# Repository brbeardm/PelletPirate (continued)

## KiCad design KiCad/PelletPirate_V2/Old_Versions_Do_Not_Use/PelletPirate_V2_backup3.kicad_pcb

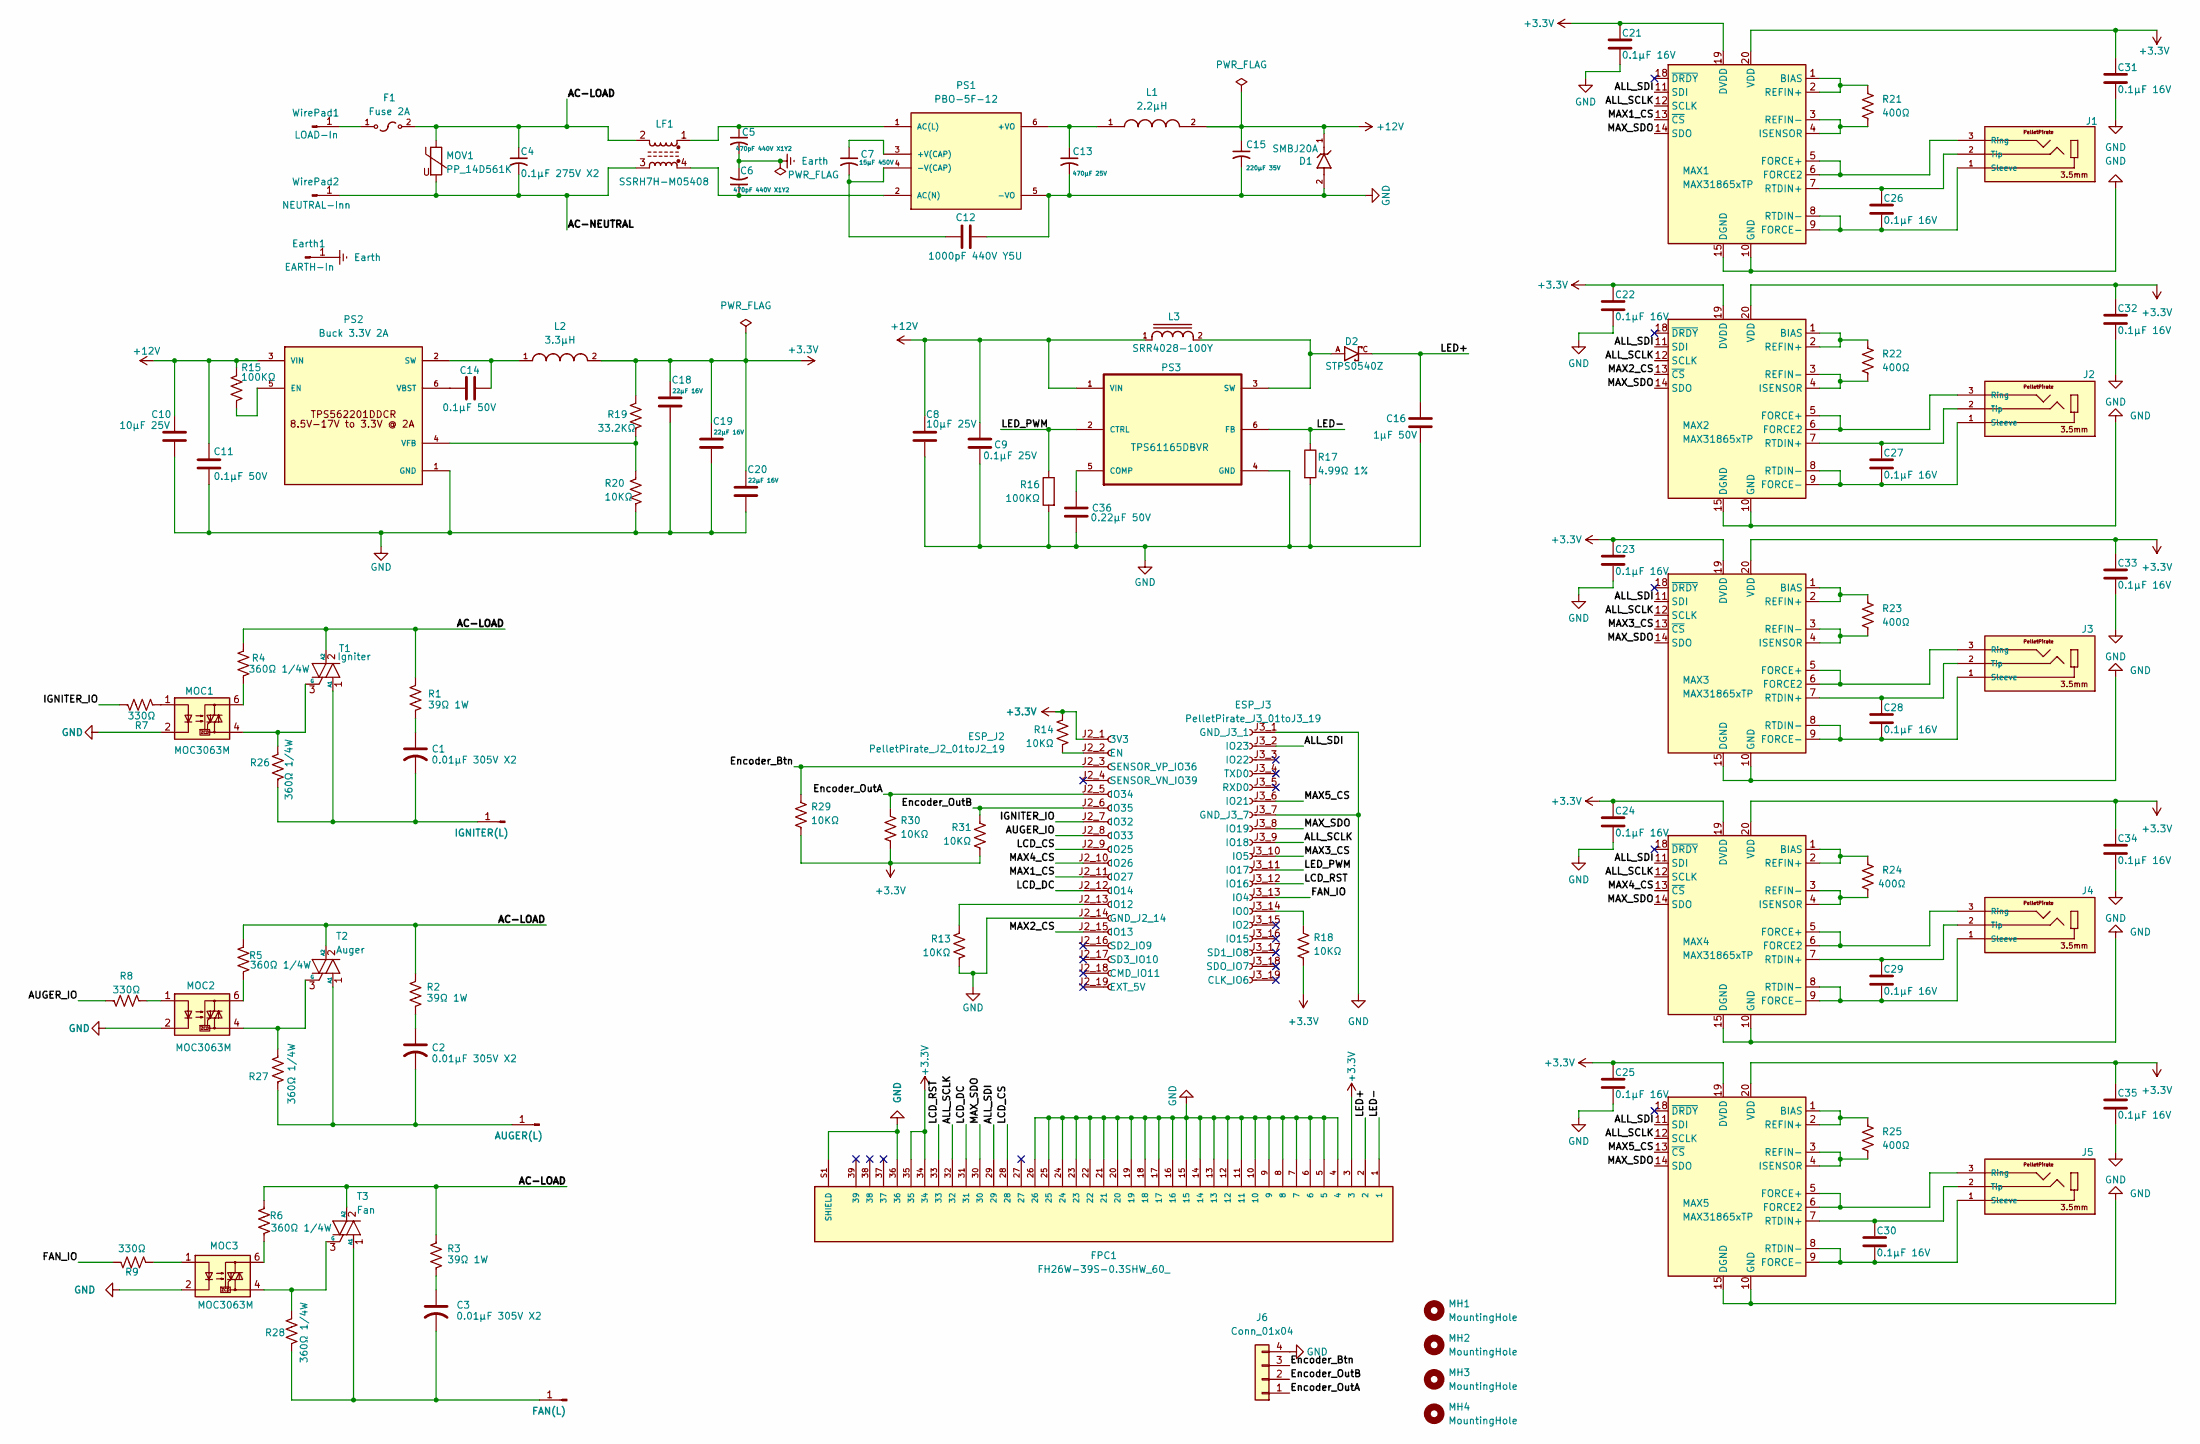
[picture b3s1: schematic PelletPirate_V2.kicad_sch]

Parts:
C1, C2, C3: 0.01µF 305V X2; C_Rect_L13.0mm_W4.0mm_P10.00mm_FKS3_FKP3_MKS4
C4: 0.1µF 275V X2; C_Rect_L13.0mm_W6.0mm_P10.00mm_FKS3_FKP3_MKS4
C5, C6: 470pF 440V X1Y2; C_Disc_D7.5mm_W5.0mm_P7.50mm
C7: 15µF 450V; CP_Radial_D10.0mm_P5.00mm
C8, C10: 10µF 25V; C_1206_3216Metric
C9: 0.1µF 25V; C_0805_2012Metric
C11, C14: 0.1µF 50V; C_0805_2012Metric
C12: 1000pF 440V Y5U; C_Disc_D7.5mm_W5.0mm_P7.50mm
C13: 470µF 25V; CP_Radial_D10.0mm_P5.00mm
C15: 220µF 35V; CP_Radial_D8.0mm_P3.50mm
C16: 1µF 50V; C_0805_2012Metric_Pad1.18x1.45mm_HandSolder
C18, C19, C20: 22µF 16V; C_1206_3216Metric
C21, C22, C23, C24, C25, C26, C27, C28, C29, C30, C31, C32, C33, C34, C35: 0.1µF 16V; C_0805_2012Metric
C36: 0.22µF 50V; C_0805_2012Metric_Pad1.18x1.45mm_HandSolder
D1: SMBJ20A; DIOM5436X261N_PelletPirate; PARTREV JC.07/04/25 v4; DigiKey_Part_Number SMBJ20ALFCT-ND
D2: STPS0540Z; SOD-123
ESP_J2: PelletPirate_J2_01toJ2_19; PinHeader_J2x19_P2.54mm_Vertical_PelletPirate
ESP_J3: PelletPirate_J3_01toJ3_19; PinHeader_J3x19_P2.54mm_Vertical_PelletPirate
Earth1: EARTH-In; SolderWire-2.5sqmm_1x01_D2.4mm_OD4.4mm
F1: Fuse 2A; SCHURTER_0031.8201; DigiKey_Part_Number 486-1258-ND
FPC1: FH26W-39S-0.3SHW_60_; HRS_FH26W-39S-0.3SHW_60_; PARTREV N/A
J1, J2, J3, J4, J5: SJ1-3523NG_Jack_PP; CUI_SJ1-3523NG_PelletPirate; PARTREV 1.01
J6: Conn_01x04; Hirose_DF13-04P-1.25DSA_1x04_P1.25mm_Vertical
L1: 2.2µH; IND_LQH3NPH2R2MMEL
L2: 3.3µH; IND_LQH43PN3R3M26L; PARTREV N/A
L3: SRR4028-100Y; SRR4028
LF1: SSRH7H-M05408; Kemet_Choke_SSRH7H_M05408
MAX1, MAX2, MAX3, MAX4, MAX5: MAX31865xTP; TQFN-20-1EP_5x5mm_P0.65mm_EP3.25x3.25mm
MH1, MH2, MH3, MH4: MountingHole; MountingHole_3.2mm_M3
MOC1, MOC2, MOC3: MOC3063M; MOC3063M-PP2
MOV1: PP_14D561K; Varistor_14mm_p7.5mm
PS1: PBO-5F-12; PBO-5F-12_pp2; PARTREV 1.0
PS2: Buck 3.3V 2A; SOT95P280X110-6N; PARTREV A
PS3: TPS61165DBVR; SOT95P280X145-6N
R1, R2, R3: 39Ω 1W; R_2512_6332Metric
R4, R5, R6, R26, R27, R28: 360Ω 1/4W; R_1206_3216Metric
R7, R8, R9: 330Ω; R_0805_2012Metric_Pad1.20x1.40mm_HandSolder
R13, R14, R18, R20, R29, R30, R31: 10KΩ; R_0805_2012Metric_Pad1.20x1.40mm_HandSolder
R15: 100KΩ; R_0805_2012Metric_Pad1.20x1.40mm_HandSolder
R16: 100KΩ; R_0603_1608Metric_Pad0.98x0.95mm_HandSolder
R17: 4.99Ω 1%; R_1206_3216Metric_Pad1.30x1.75mm_HandSolder
R19: 33.2KΩ; R_0805_2012Metric_Pad1.20x1.40mm_HandSolder
R21, R22, R23, R24, R25: 400Ω; R_1206_3216Metric
T1: Igniter; TO-220-3_Vertical
T2: Auger; TO-220-3_Vertical
T3: Fan; TO-220-3_Vertical
WirePad1: LOAD-In; SolderWire-2.5sqmm_1x01_D2.4mm_OD4.4mm
WirePad2: NEUTRAL-Inn; SolderWire-2.5sqmm_1x01_D2.4mm_OD4.4mm
WirePad3: IGNITER(L); SolderWire-2.5sqmm_1x01_D2.4mm_OD3.6mm
WirePad4: AUGER(L); SolderWire-2.5sqmm_1x01_D2.4mm_OD3.6mm
WirePad5: FAN(L); SolderWire-2.5sqmm_1x01_D2.4mm_OD3.6mm

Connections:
+3.3V: C18.1, C19.1, C20.1, C21.2, C22.2, C23.2, C24.2, C25.2, C31.2, C32.2, C33.2, C34.2, C35.2, ESP_J2.J2_1 (3V3), FPC1.3, FPC1.34, FPC1.35, L2.2, MAX1.19 (DVDD), MAX1.20 (VDD), MAX2.19 (DVDD), MAX2.20 (VDD), MAX3.19 (DVDD), MAX3.20 (VDD), MAX4.19 (DVDD), MAX4.20 (VDD), MAX5.19 (DVDD), MAX5.20 (VDD), R14.1, R18.2, R19.1, R29.2, R30.2, R31.2; also elsewhere on the board
+12V: C8.1, C9.1, C10.1, C11.2, C15.1, D1.1, L1.2, L3.1, PS2.3 (VIN), PS3.1 (VIN), R15.1
/AC-LOAD: C4.1, F1.2, LF1.2, MOV1.1, R1.1, R2.1, R3.1, R4.2, R5.2, R6.1, T1.2 (A2), T2.2 (A2), T3.2 (A2)
/AC-NEUTRAL: C4.2, LF1.3, MOV1.2, WirePad2.1 (Pin_1_1); also elsewhere on the board
/ALL_SCLK: ESP_J3.J3_9 (IO18), FPC1.32, MAX1.12 (SCLK), MAX2.12 (SCLK), MAX3.12 (SCLK), MAX4.12 (SCLK), MAX5.12 (SCLK); also elsewhere on the board
/ALL_SDI: ESP_J3.J3_2 (IO23), FPC1.29, MAX1.11 (SDI), MAX2.11 (SDI), MAX3.11 (SDI), MAX4.11 (SDI), MAX5.11 (SDI); also elsewhere on the board
/AUGER_IO: ESP_J2.J2_8 (IO33), R8.2; also elsewhere on the board
/Encoder_Btn: ESP_J2.J2_3 (SENSOR_VP_IO36), J6.3, R29.1; also elsewhere on the board
/Encoder_OutA: ESP_J2.J2_5 (IO34), J6.1, R30.1; also elsewhere on the board
/Encoder_OutB: ESP_J2.J2_6 (IO35), J6.2, R31.1; also elsewhere on the board
/FAN_IO: ESP_J3.J3_13 (IO4), R9.1; also elsewhere on the board
/IGNITER_IO: ESP_J2.J2_7 (IO32), R7.2; also elsewhere on the board
/LCD_CS: ESP_J2.J2_9 (IO25), FPC1.28; also elsewhere on the board
/LCD_DC: ESP_J2.J2_12 (IO14), FPC1.31; also elsewhere on the board
/LCD_RST: ESP_J3.J3_12 (IO16), FPC1.33; also elsewhere on the board
/LED+: C16.1, D2.C, FPC1.2
/LED-: FPC1.1, PS3.6 (FB), R17.1
/LED_PWM: ESP_J3.J3_11 (IO17), PS3.2 (CTRL), R16.1; also elsewhere on the board
/MAX1_CS: ESP_J2.J2_11 (IO27), MAX1.13 (~CS); also elsewhere on the board
/MAX2_CS: ESP_J2.J2_15 (IO13), MAX2.13 (~CS); also elsewhere on the board
/MAX3_CS: ESP_J3.J3_10 (IO5), MAX3.13 (~CS); also elsewhere on the board
/MAX4_CS: ESP_J2.J2_10 (IO26), MAX4.13 (~CS); also elsewhere on the board
/MAX5_CS: ESP_J3.J3_6 (IO21), MAX5.13 (~CS); also elsewhere on the board
/MAX_SDO: ESP_J3.J3_8 (IO19), FPC1.30, MAX1.14 (SDO), MAX2.14 (SDO), MAX3.14 (SDO), MAX4.14 (SDO), MAX5.14 (SDO); also elsewhere on the board
Earth: C5.2, C6.2, Earth1.1 (Pin_1_1)
GND: C8.2, C9.2, C10.2, C11.1, C12.2, C13.2, C15.2, C16.2, C18.2, C19.2, C20.2, C21.1, C22.1, C23.1, C24.1, C25.1, C31.1, C32.1, C33.1, C34.1, C35.1, C36.2, D1.2, ESP_J2.J2_14 (GND_J2_14), ESP_J3.J3_1 (GND_J3_1), ESP_J3.J3_7 (GND_J3_7), FPC1.4, FPC1.5, FPC1.6, FPC1.7, FPC1.8, FPC1.9, FPC1.10, FPC1.11, FPC1.12, FPC1.13, FPC1.14, FPC1.15, FPC1.16, FPC1.17, FPC1.18, FPC1.19, FPC1.20, FPC1.21, FPC1.22, FPC1.23, FPC1.24, FPC1.25, FPC1.26, FPC1.36, FPC1.S1 (SHIELD), FPC1.S2 (SHIELD), J6.4, MAX1.10 (GND), MAX1.15 (DGND), MAX1.16 (GND), MAX1.21 (GND), MAX2.10 (GND), MAX2.15 (DGND), MAX2.16 (GND), MAX2.21 (GND), MAX3.10 (GND), MAX3.15 (DGND), MAX3.16 (GND), MAX3.21 (GND), MAX4.10 (GND), MAX4.15 (DGND), MAX4.16 (GND), MAX4.21 (GND), MAX5.10 (GND), MAX5.15 (DGND), MAX5.16 (GND), MAX5.21 (GND), MOC1.2, MOC2.2, MOC3.2, PS1.5 (-VO), PS2.1 (GND), PS3.4 (GND), R13.2, R16.2, R17.2, R20.2; also elsewhere on the board
unnamed: C1.1, R1.2
unnamed: C2.1, R2.2
unnamed: C3.1, R3.2
unnamed 29: ESP_J2.J2_2 (EN), R14.2; also elsewhere on the board
unnamed 30: ESP_J3.J3_14 (IO0), R18.1; also elsewhere on the board
unnamed 31: ESP_J2.J2_13 (IO12), R13.1; also elsewhere on the board
unnamed: J1.3 (Ring), MAX1.5 (FORCE+), MAX1.6 (FORCE2)
unnamed: C26.1, J1.1 (Sleeve), MAX1.8 (RTDIN-), MAX1.9 (FORCE-)
unnamed: C26.2, J1.2 (Tip), MAX1.7 (RTDIN+)
unnamed: J2.3 (Ring), MAX2.5 (FORCE+), MAX2.6 (FORCE2)
unnamed: C27.1, J2.1 (Sleeve), MAX2.8 (RTDIN-), MAX2.9 (FORCE-)
unnamed: C27.2, J2.2 (Tip), MAX2.7 (RTDIN+)
unnamed: J3.3 (Ring), MAX3.5 (FORCE+), MAX3.6 (FORCE2)
unnamed: C28.1, J3.1 (Sleeve), MAX3.8 (RTDIN-), MAX3.9 (FORCE-)
unnamed: C28.2, J3.2 (Tip), MAX3.7 (RTDIN+)
unnamed: J4.3 (Ring), MAX4.5 (FORCE+), MAX4.6 (FORCE2)
unnamed: C29.1, J4.1 (Sleeve), MAX4.8 (RTDIN-), MAX4.9 (FORCE-)
unnamed: C29.2, J4.2 (Tip), MAX4.7 (RTDIN+)
unnamed: J5.3 (Ring), MAX5.5 (FORCE+), MAX5.6 (FORCE2)
unnamed: C30.1, J5.1 (Sleeve), MAX5.8 (RTDIN-), MAX5.9 (FORCE-)
unnamed: C30.2, J5.2 (Tip), MAX5.7 (RTDIN+)
unnamed: MAX1.1 (BIAS), MAX1.2 (REFIN+), R21.1
unnamed: MAX1.3 (REFIN-), MAX1.4 (ISENSOR), R21.2
unnamed: MAX2.1 (BIAS), MAX2.2 (REFIN+), R22.1
unnamed: MAX2.3 (REFIN-), MAX2.4 (ISENSOR), R22.2
unnamed: MAX3.1 (BIAS), MAX3.2 (REFIN+), R23.1
unnamed: MAX3.3 (REFIN-), MAX3.4 (ISENSOR), R23.2
unnamed: MAX4.1 (BIAS), MAX4.2 (REFIN+), R24.1
unnamed: MAX4.3 (REFIN-), MAX4.4 (ISENSOR), R24.2
unnamed: MAX5.1 (BIAS), MAX5.2 (REFIN+), R25.1
unnamed: MAX5.3 (REFIN-), MAX5.4 (ISENSOR), R25.2
unnamed: MOC1.1, R7.1
unnamed: MOC1.6, R4.1
unnamed: MOC2.1, R8.1
unnamed: MOC2.6, R5.1
unnamed: MOC3.1, R9.2
unnamed: MOC3.6, R6.2
unnamed: C7.1, PS1.3 (+V(CAP))
unnamed: C13.1, L1.1, PS1.6 (+VO)
unnamed: C7.2, C12.1, PS1.4 (-V(CAP))
unnamed: C5.1, LF1.1, PS1.1 (AC(L))
unnamed: C6.1, LF1.4, PS1.2 (AC(N))
unnamed: PS2.5 (EN), R15.2
unnamed: C14.2, L2.1, PS2.2 (SW)
unnamed: C14.1, PS2.6 (VBST)
unnamed: PS2.4 (VFB), R19.2, R20.1
unnamed: C36.1, PS3.5 (COMP)
unnamed: D2.A, L3.2, PS3.3 (SW)
unnamed: C1.2, R26.2, T1.1 (A1), WirePad3.1 (Pin_1_1)
unnamed: MOC1.4, R26.1, T1.3 (G)
unnamed: C2.2, R27.2, T2.1 (A1), WirePad4.1 (Pin_1_1)
unnamed: MOC2.4, R27.1, T2.3 (G)
unnamed: C3.2, R28.2, T3.1 (A1), WirePad5.1 (Pin_1_1)
unnamed: MOC3.4, R28.1, T3.3 (G)
unnamed: F1.1, WirePad1.1 (Pin_1_1)

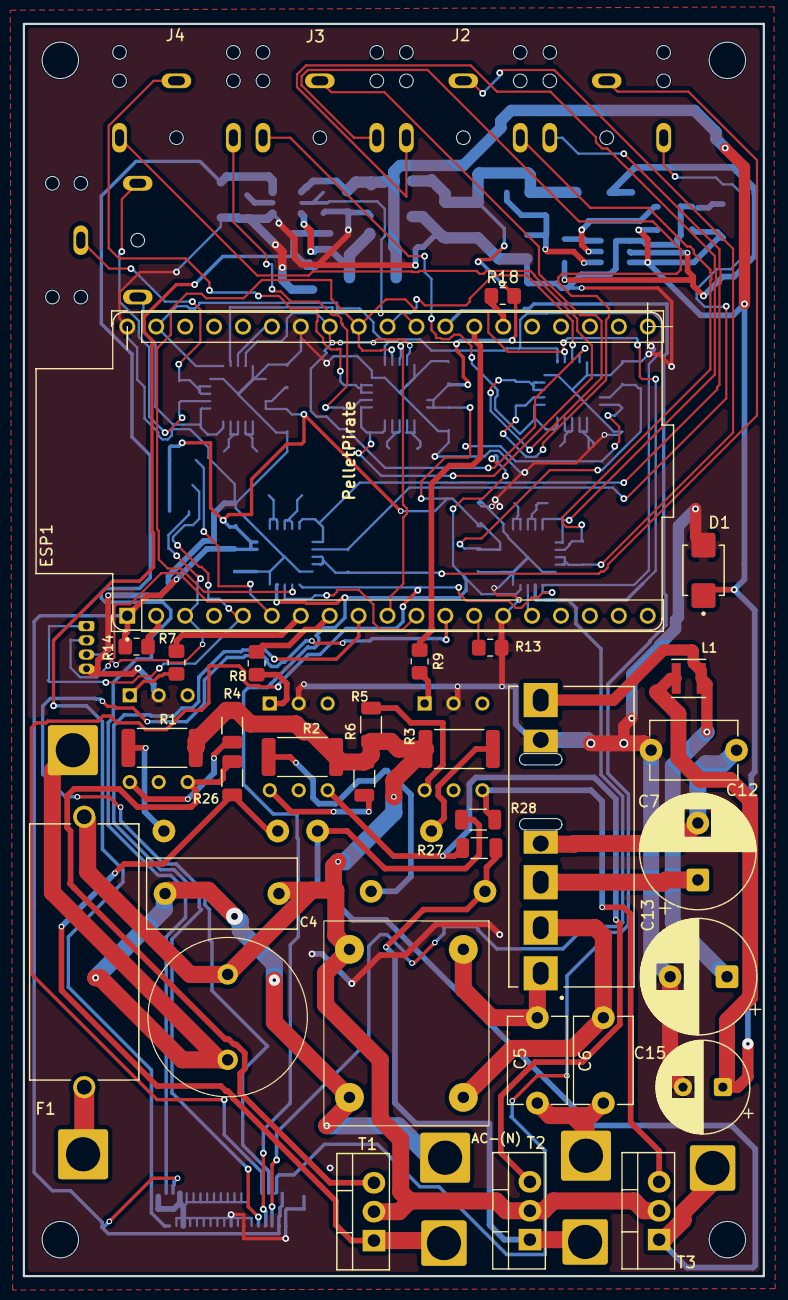
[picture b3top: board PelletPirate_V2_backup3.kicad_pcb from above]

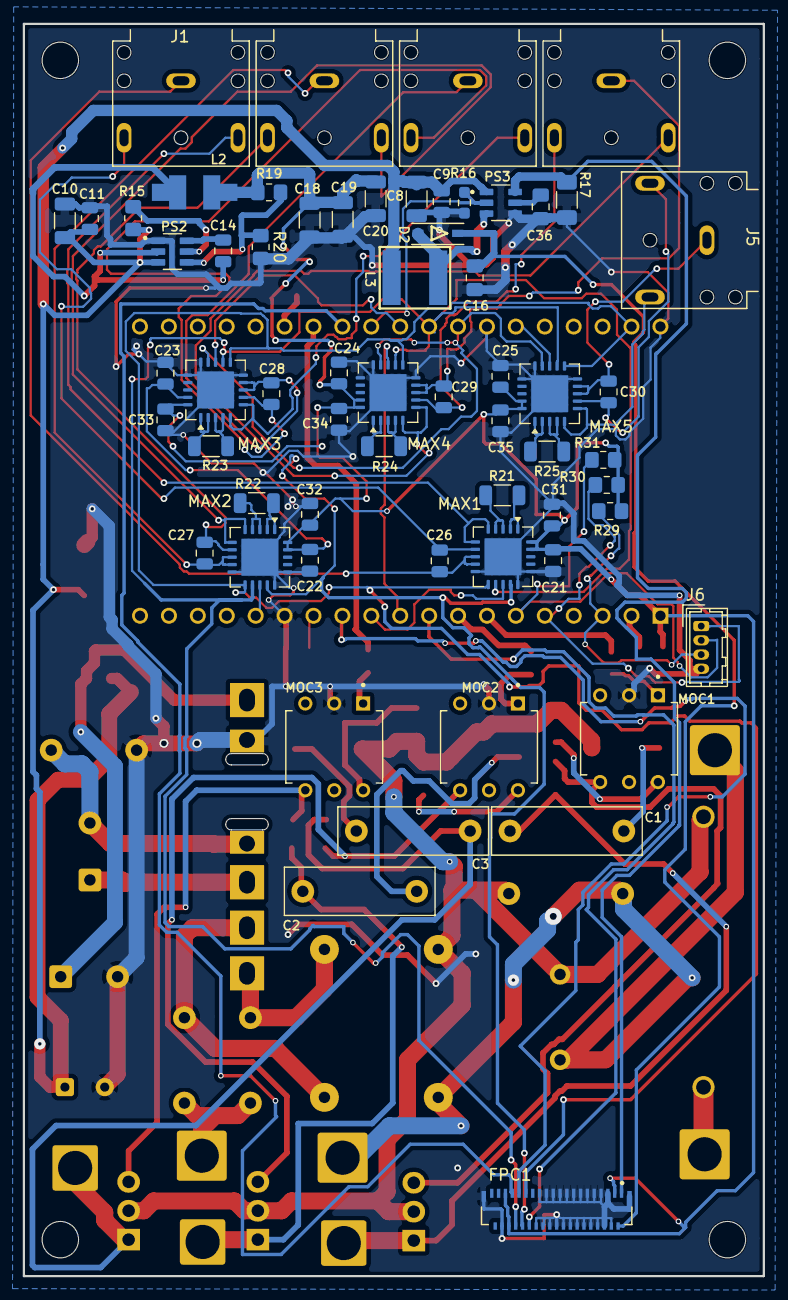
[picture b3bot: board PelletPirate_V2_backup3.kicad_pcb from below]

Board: 2 copper layers, 65.0 x 110.0 mm, 104 parts (61 on the bottom side), 81 nets.

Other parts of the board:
AC-(N): AC-NEUTRAL; SolderWire-2.5sqmm_1x01_D2.4mm_OD4.4mm
ESP1: ESP32-DEVKITC-32E_PelletPirate; ESP32-PelletPirate-02x19x2-female-rail-sockets

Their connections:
+3.3V: ESP1.J2_1 (3V3); also elsewhere on the board
/AC-NEUTRAL: AC-(N).1 (Pin_1_1); also elsewhere on the board
/ALL_SCLK: ESP1.J3_9 (IO18); also elsewhere on the board
/ALL_SDI: ESP1.J3_2 (IO23); also elsewhere on the board
/AUGER_IO: ESP1.J2_8 (IO33); also elsewhere on the board
/Encoder_Btn: ESP1.J2_3 (SENSOR_VP_IO36); also elsewhere on the board
/Encoder_OutA: ESP1.J2_5 (IO34); also elsewhere on the board
/Encoder_OutB: ESP1.J2_6 (IO35); also elsewhere on the board
/FAN_IO: ESP1.J3_13 (IO4); also elsewhere on the board
/IGNITER_IO: ESP1.J2_7 (IO32); also elsewhere on the board
/LCD_CS: ESP1.J2_9 (IO25); also elsewhere on the board
/LCD_DC: ESP1.J2_12 (IO14); also elsewhere on the board
/LCD_RST: ESP1.J3_12 (IO16); also elsewhere on the board
/LED_PWM: ESP1.J3_11 (IO17); also elsewhere on the board
/MAX1_CS: ESP1.J2_11 (IO27); also elsewhere on the board
/MAX2_CS: ESP1.J2_15 (IO13); also elsewhere on the board
/MAX3_CS: ESP1.J3_10 (IO5); also elsewhere on the board
/MAX4_CS: ESP1.J2_10 (IO26); also elsewhere on the board
/MAX5_CS: ESP1.J3_6 (IO21); also elsewhere on the board
/MAX_SDO: ESP1.J3_8 (IO19); also elsewhere on the board
GND: ESP1.J2_14 (GND_J2_14), ESP1.J3_1 (GND_J3_1), ESP1.J3_7 (GND_J3_7); also elsewhere on the board
unnamed 29: ESP1.J2_2 (EN); also elsewhere on the board
unnamed 30: ESP1.J3_14 (IO0); also elsewhere on the board
unnamed 31: ESP1.J2_13 (IO12); also elsewhere on the board

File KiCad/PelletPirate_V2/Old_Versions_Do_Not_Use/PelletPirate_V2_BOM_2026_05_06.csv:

,,,Reference,Qty,Value,Voltage / Watts,Manufacturer Part Number,Digitkey Part Number Link,,Footprint,
,,15,"C1,C2,C3",3,0.01µF 305V X2 Film,305V,B32921C3103M026,495-B32921C3103M026-ND,FILM CAP MKP X2 0.010UF 20% 305V,Capacitor_THT:C_Rect_L13.0mm_W4.0mm_P10.00mm_FKS3_FKP3_MKS4,
,,,C4,1,0.1µF 275V X2,,,,,Capacitors:CAPRR1500W80L1800T500H1050,
,,,"C5,C6",2,470pF 250V Y2,,,,,Capacitor_THT:C_Disc_D7.5mm_W5.0mm_P7.50mm,
,,,C7,1,15µF 450V,,,,,Capacitor_THT:CP_Radial_D10.0mm_P5.00mm,
,,5,C8,1,10µF,25V,C1206C106K3RACTU,399-C1206C106K3RACTUCT-ND,CAP CER 10UF 25V X7R 1206,Capacitor_SMD:C_1206_3216Metric,
,,5,C9,1,100nF,25V,C0805C104K3RACTU,399-C0805C104K3RACTUCT-ND,CAP CER 0.1UF 25V X7R 0805,Capacitor_SMD:C_0805_2012Metric,
,,,C10,1,10uf 25V,,,,,Capacitor_SMD:C_0805_2012Metric,
,,,"C11,C14",2,0.1uF 50V,,,,,Capacitor_SMD:C_0805_2012Metric,
,,,C12,1,1000pF 440V Y2,,,,,Capacitor_THT:C_Disc_D7.5mm_W5.0mm_P7.50mm,
,,,C13,1,470µF 25V,,,,,Capacitor_THT:CP_Radial_D10.0mm_P5.00mm,
,,,C15,1,220µF 35V,,,,,Capacitor_THT:CP_Radial_D8.0mm_P3.50mm,
,,5,C16,1,1uF 50V,50V,C0805C105K5RACTU,399-C0805C105K5RACTUCT-ND,CAP CER 1UF 50V X7R 0805,Capacitor_SMD:C_0805_2012Metric_Pad1.18x1.45mm_HandSolder,
,,,"C18,C19,C20",3,22uF 16V,,,,,Capacitor_SMD:C_1206_3216Metric,
,,50,"C21,C22,C23,C24,C25,C26,C27,C28,C29,C30,C31,C32,C33,C34,C35",15,0.1uF 16V X7R,16V,CC0805KRX7R7BB104,311-1142-1-ND,CAP CER 0.1UF 16V X7R 0805,Capacitor_SMD:C_0805_2012Metric,
,,,C36,1,220nF,,,,,Capacitor_SMD:C_0805_2012Metric_Pad1.18x1.45mm_HandSolder,
,,,D1,1,SMBJ20A,,,,,SMBJ20A_PelletPirate:DIOM5436X261N_PelletPirate,
,,,D2,1,STPS0540Z,,,,,STPS0540Z_Schotty Diode LED:SOD-123,
,,,ESP1,1,ESP32-DEVKITC-32E_PelletPirate,,,,,ESP32-DevKitC-32E_PelletPirate:MODULE_ESP32-DEVKITC-32E_PelletPirate,
5,,,F1,1,Fuse 2A,500V,31.8201,486-1258-ND,FUSE BLOK CARTRIDGE 500V 16A PCB,0031.8201:SCHURTER_0031.8201,
,,3,FPC1,1,FH26W-39S-0.3SHW_60_,n/a,FH26W-39S-0.3SHW(60),H125803CT-ND,CONN FPC BOTTOM 39POS 0.3MM R/A,FPC_Connector_HiRose:HRS_FH26W-39S-0.3SHW_60_,
,,,"J1,J2,J3,J4,J5",5,SJ1-3523NG_Jack_PP,,,,,3.5mm_Jacks:CUI_SJ1-3523NG_PelletPirate,
,,,J6,1,Conn_01x04,,,,,Connector_Hirose:Hirose_DF13-04P-1.25DSA_1x04_P1.25mm_Vertical,
,,5,L1,1,2.2µH,2.1A,LQH3NPH2R2MMEL,490-LQH3NPH2R2MMELCT-ND,FIXED IND 2.2UH 2.1A 78 MOHM SMD,Inductor_SMD:L_2512_6332Metric,
,,,L2,1,3.3µH,,,,,Inductor_SMD:L_2512_6332Metric,
,,5,L3,1,SRR4028-100Y,1.19A,SRR4028-100Y,SRR4028-100YCT-ND,FIXED IND 10UH 1.19A 110 MOHM,Inductors:SRR4028,
5,,,LF1,1,SSRH7H-M05408,500MA,SSRH7H-M05408,399-17043-ND,CMC 40.8MH 500MA 2LN TH,Kermit_Choke_SSRH7H_MO5408:Kemet_Choke_SSRH7H_M05408,
,,,"MAX1,MAX2,MAX3,MAX4,MAX5",5,MAX31865xTP,,,,,Package_DFN_QFN:TQFN-20-1EP_5x5mm_P0.65mm_EP3.25x3.25mm,
,,,MOC1,1,IGNITER,,,,,MOC3063M-PP2:MOC3063M-PP2,
,,,MOC2,1,AUGER,,,,,MOC3063M-PP2:MOC3063M-PP2,
,,,MOC3,1,FAN,,,,,MOC3063M-PP2:MOC3063M-PP2,
5,,,MOV1,1,PP_14D561K,560V 4.5KA,MOV-14D561K,118-MOV-14D561K-ND,VARISTOR 560V 4.5KA DISC 14MM,Varistors_PelletPirate:Varistor_14mm_p7.5mm,
,,,PS1,1,PBO-5F-12,,,,,PBO-5F-12_PP_Try2:PBO-5F-12_pp2,
,,,PS2,1,Buck 3.3V 2A,,,,,Buck_3.3V:SOT95P280X110-6N,
,,5,PS3,1,TPS61165DBVR,IC LED DRV SOT23-6,TPS61165DBVR,296-27597-1-ND,IC LED DRV RGLTR PWM SOT23-6,LED_Driver:SOT95P280X145-6N,
,,15,"R1,R2,R3",3,39? 1W,1W,CRCW251239R0FKEG,541-39.0AFCT-ND,RES SMD 39 OHM 1% 1W 2512,Resistor_SMD:R_2512_6332Metric,
,,18,"R4,R5,R6,R26,R27,R28",6,360? 1/4W,1/4W,CRCW1206360RFKEA,541-360FCT-ND,RES SMD 360 OHM 1% 1/4W 1206,Resistor_SMD:R_1206_3216Metric,
,,,"R7,R8,R9",3,330?,,,,,Resistor_SMD:R_0805_2012Metric_Pad1.20x1.40mm_HandSolder,
,,10,"R13,R14,R18,R20,R29,R30,R31",7,10K? 1%,1/8W,RC0805FR-0710KL,311-10.0KCRCT-ND,RES 10K OHM 1% 1/8W 0805,Resistor_SMD:R_0805_2012Metric_Pad1.20x1.40mm_HandSolder,
,,,R15,1,100K?,,,,,Resistor_SMD:R_0805_2012Metric_Pad1.20x1.40mm_HandSolder,
,,,R16,1,100K?,,,,,Resistor_SMD:R_0603_1608Metric_Pad0.98x0.95mm_HandSolder,
,,,R17,1,4.99? 1%,,,,,Resistor_SMD:R_1206_3216Metric_Pad1.30x1.75mm_HandSolder,
,,,R19,1,33.2K,,,,,Resistor_SMD:R_0805_2012Metric_Pad1.20x1.40mm_HandSolder,
,,25,"R21,R22,R23,R24,R25",5,400?,1/4W,RT1206BRD07400RL,13-RT1206BRD07400RLCT-ND,RES SMD 400 OHM 0.1% 1/4W 1206,Resistor_SMD:R_1206_3216Metric,
,,,"T1,T2,T3",3,BTA12-Triac,,,,,Package_TO_SOT_THT:TO-220-3_Vertical,
,,,,,,,,,,,
,,10,,,Wire - Blue,n/a,H4BXG-10106-L8,H4BXG-10106-L8-ND,"JUMPER-H9991TR/1852BL/X 6""",n/a,
,,10,,,Wire - Orange,n/a,H4BXG-10106-A8,H4BXG-10106-A8-ND,"JUMPER-H9991TR/1852OR/X 6""",n/a,
,,10,,,Wire - Yellow,n/a,H4BXG-10106-Y8,H4BXG-10106-Y8-ND,"JUMPER-H9991TR/1852YL/X 6""",n/a,
,,10,,,Wire - Black,n/a,H4BXG-10106-B8,H4BXG-10106-B8-ND,"JUMPER-H9991TR/1852BK/X 6""",n/a,
,,5,,,Male 4POS encoder plug,n/a,DF13-4S-1.25C,H2181-ND,CONN RCPT HSG 4POS 1.25MM,n/a,
,,5,,,Female 4POS encoder plug,n/a,DF13A-4P-1.25H(51),H125779CT-ND,CONN HEADER SMD R/A 4POS 1.25MM,n/a,
5,,,,,2A glass fast-blow fuses,250V 2A,VBS UBM 2A 250V (PF),4598-VBSUBM2A250V(PF)-ND,FUSE CERAMIC 2A 250VAC 5X20MM,n/a,
,,,,,,,,,,,
,,,,,,,,,,,
,,,,,,,,,,,
,,,Returns,,,,,,,,
,,,,5,,,PBO-5F-5,,"AC-DC, 5 W, 5 VDC, SINGLE OUTPUT",,
,,,,5,,,SMBJ7.0A,,TVS DIODE 7VWM 12VC DO214AA,,
,,,,5,,,78F2R2J-RC,,FIXED IND 2.2UH 630MA 250 MOHM,,
